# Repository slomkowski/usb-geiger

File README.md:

# USB Geiger counter

2013 Michał Słomkowski

License: GNU GPL v3.0.

This is a repository of a low-cost USB Geiger counter device using STS-5 tube, ATTiny24 and Python-written host software.

Results can be sent to MySQL database, CSV file, ~~xively.com~~ or defined e-mail address if the radiation level is above the defined threshold.

Project was published in Polish hobby electronics periodic: *Elektronika dla Wszystkich* 10/2013, the article [available here](https://serwis.avt.pl/manuals/AVT3074.pdf).

The repository contains:
* *datasheets* - datasheets of components used in the device, especially the Geiger tube
* *firmare* - source code of firmware for ATTiny24, written in C
* *host/geiger-controller* - simple program in C++ for reading data and writing the settings to the device
* *host/geiger-manager* - more complex software written in Python. Periodically reads the data from sensor and sends them to MySQL or CSV file
* *pcb* - printed circuit board layout in Eagle format, schematic in PNG and mirrored board layout for toner transfer

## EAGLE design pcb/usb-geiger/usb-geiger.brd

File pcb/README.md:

USB Geiger counter
==================

2013 Michał Słomkowski

License: GNU GPL v3.0.

This directory holds circuit board files created in Eagle 6 as well as result files: PDF with mirror image and PNG schematic.

Warning! You need commercial version of Eagle to modify the board. Using freeware version, you may be only able to move elements within area of 80 x 100 mm. This restriction doesn't apply to other tasks like printing, exporting or value changing, though.

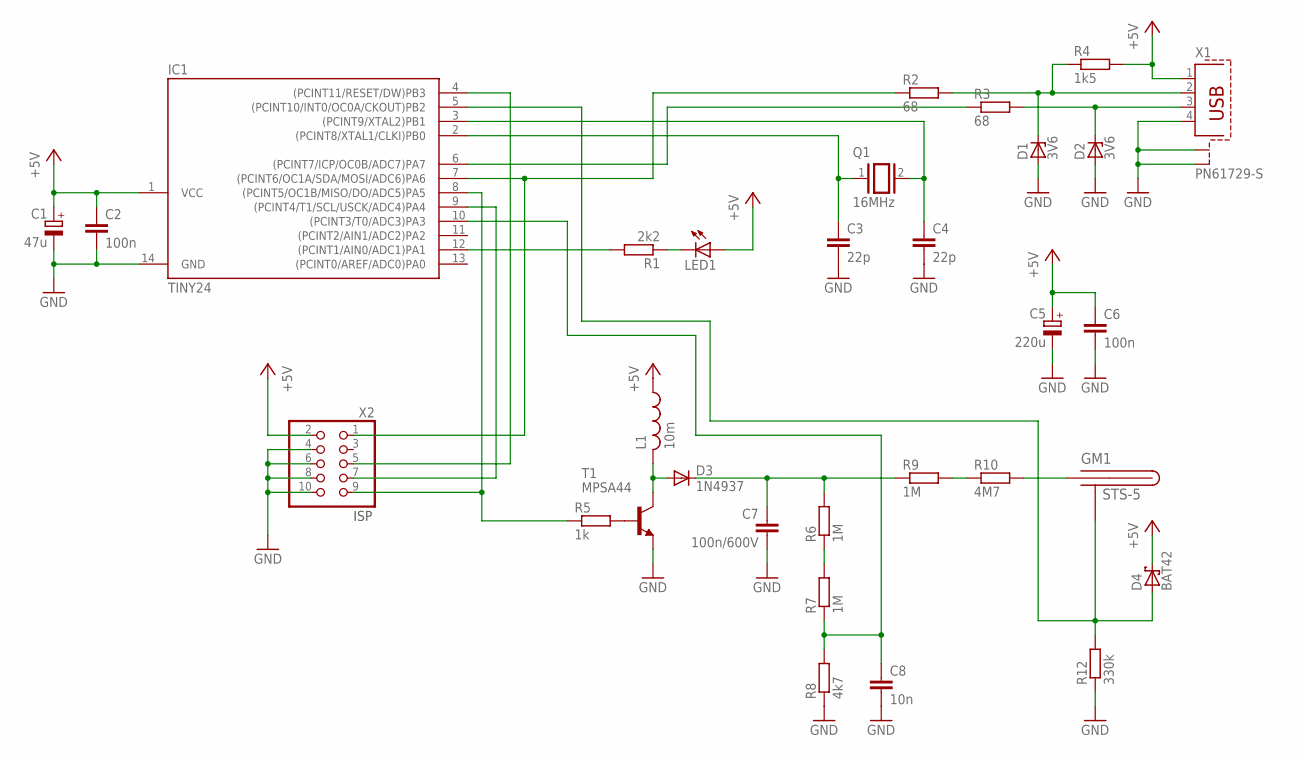
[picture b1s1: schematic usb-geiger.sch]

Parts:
C1: 47u; E2,5-6
C2, C6: 100n; C050-025X075
C3, C4: 22p; C025-025X050
C5: 220u; E5-10,5
C7: 100n/600V; C225-113X268
C8: 10n; C050-025X075
D1, D2: 3V6; DO34Z7
D3: 1N4937; DO41-10
D4: BAT42; DO35-10
GM1: STS-5
IC1: TINY24; DIL14
L1: 10m; 0207/5V
LED1: LED3MM
Q1: 16MHz; QS
R1: 2k2; 0207/10
R2, R3: 68; 0207/10
R4: 1k5; 0207/10
R5: 1k; 0207/10
R6, R7, R9: 1M; 0207/10
R8: 4k7; 0207/10
R10: 4M7; 0207/10
R12: 330k; 0207/10
T1: MPSA44; TO92-EBC
X1: PN61729-S
X2: PINHD-2X5; 2X05

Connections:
+5V: C1.+, C2.1, C5.+, C6.1, D4.C, IC1.1 (VCC), L1.1, LED1.A, R4.2, X1.1, X2.2
GND: C1.-, C2.2, C3.2, C4.2, C5.-, C6.2, C7.2, C8.2, D1.A, D2.A, IC1.14 (GND), R8.1, R12.1, T1.E, X1.4, X1.S1, X1.S2, X2.4, X2.6, X2.8, X2.10
unnamed: R6.1, R7.2
unnamed: D3.A, L1.2, T1.C
unnamed: R5.2, T1.B
unnamed: C7.1, D3.C, R6.2, R9.1
unnamed: R9.2, R10.1
unnamed: GM1.PLUS1 (PLUS), GM1.PLUS2 (PLUS), R10.2
unnamed: C8.1, IC1.10 ((PCINT3/T0/ADC3)PA3), R7.1, R8.2
unnamed: IC1.6 ((PCINT7/ICP/OC0B/ADC7)PA7), R3.1
unnamed: D4.A, GM1.MINUS1 (MINUS), GM1.MINUS2 (MINUS), IC1.5 ((PCINT10/INT0/OC0A/CKOUT)PB2), R12.2
unnamed: IC1.8 ((PCINT5/OC1B/MISO/DO/ADC5)PA5), R5.1, X2.9
unnamed: IC1.7 ((PCINT6/OC1A/SDA/MOSI/ADC6)PA6), R2.1, X2.1
unnamed: IC1.4 ((PCINT11/RESET/DW)PB3), X2.5
unnamed: IC1.9 ((PCINT4/T1/SCL/USCK/ADC4)PA4), X2.7
unnamed: D1.C, R2.2, R4.1, X1.2
unnamed: D2.C, R3.2, X1.3
unnamed: C4.1, IC1.3 ((PCINT9/XTAL2)PB1), Q1.2
unnamed: C3.1, IC1.2 ((PCINT8/XTAL1/CLKI)PB0), Q1.1
unnamed: IC1.12 ((PCINT1/AIN0/ADC1)PA1), R1.2
unnamed: LED1.K (C), R1.1

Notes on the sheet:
ISP

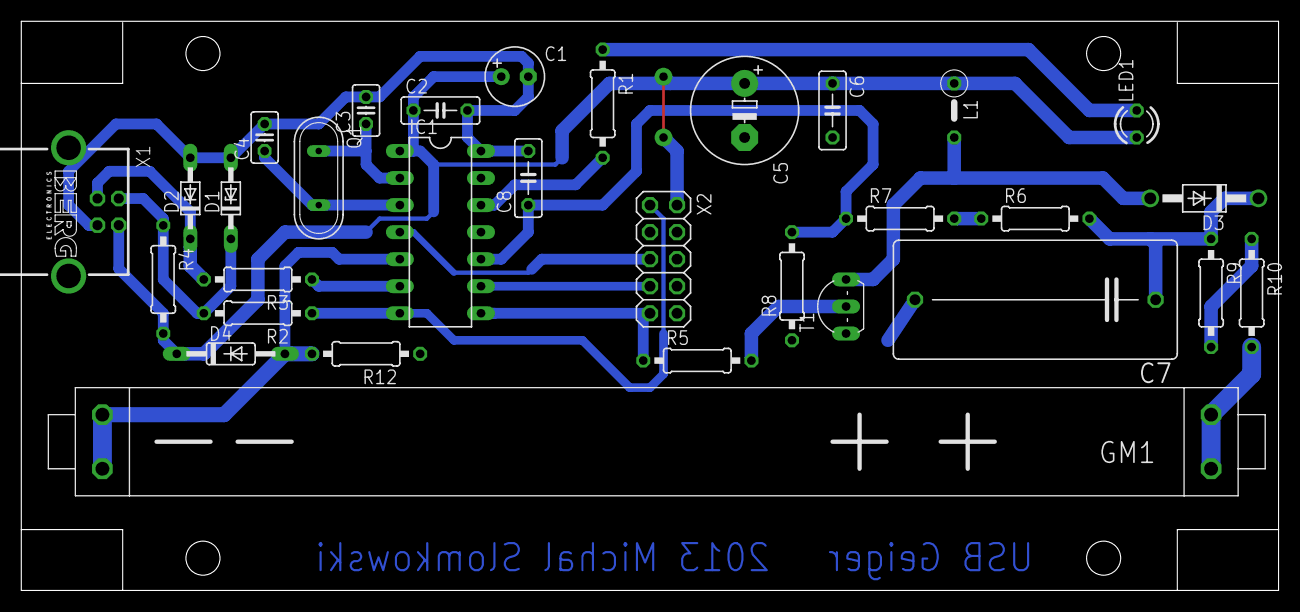
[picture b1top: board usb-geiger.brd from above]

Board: 2 copper layers, 118.1 x 53.5 mm, 31 parts (0 on the bottom side), 21 nets.

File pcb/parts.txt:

Partlist

Exported from usb-geiger.sch at 24-03-2013 21:28

EAGLE Version 6.4.0 Copyright (c) 1988-2013 CadSoft

Assembly variant: 

Part     Value          Device            Package      Library  Sheet

C1       47u            CPOL-EUE2.5-6     E2,5-6       rcl      1
C2       100n           C-EU050-025X075   C050-025X075 rcl      1
C3       22p            C-EU025-025X050   C025-025X050 rcl      1
C4       22p            C-EU025-025X050   C025-025X050 rcl      1
C5       220u           CPOL-EUE5-10.5    E5-10,5      rcl      1
C6       100n           C-EU050-025X075   C050-025X075 rcl      1
C7       100n/600V      C-EU225-113X268   C225-113X268 rcl      1
C8       10n            C-EU050-025X075   C050-025X075 rcl      1
D1       3V6            ZENER-DIODEDO34-7 DO34Z7       diode    1
D2       3V6            ZENER-DIODEDO34-7 DO34Z7       diode    1
D3       1N4937         1N4933            DO41-10      diode    1
D4       BAT42          BAT42             DO35-10      diode    1
GM1      STS-5          STS-5             STS-5        geiger   1
IC1      TINY24         TINY24/44/84-PU   DIL14        avr-7    1
L1       10m            L-US0207/5V       0207/5V      rcl      1
LED1                    LED3MM            LED3MM       led      1
Q1       16MHz          XTAL/S            QS           special  1
R1       2k2            R-EU_0207/10      0207/10      rcl      1
R2       68             R-EU_0207/10      0207/10      rcl      1
R3       68             R-EU_0207/10      0207/10      rcl      1
R4       1k5            R-EU_0207/10      0207/10      rcl      1
R5       1k             R-EU_0207/10      0207/10      rcl      1
R6       1M             R-EU_0207/10      0207/10      rcl      1
R7       1M             R-EU_0207/10      0207/10      rcl      1
R8       4k7            R-EU_0207/10      0207/10      rcl      1
R9       1M             R-EU_0207/10      0207/10      rcl      1
R10      4M7            R-EU_0207/10      0207/10      rcl      1
R12      330k           R-EU_0207/10      0207/10      rcl      1
T1       MPSA44         MPSA44            TO92-EBC     geiger   1
X1       PN61729-S      PN61729-S         PN61729-S    con-berg 1
X2                      PINHD-2X5         2X05         pinhead  1

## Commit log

2013-03-24 First commit. Firmware and board completed and tested. C++ host side completed.
2013-03-24 removed polish sentence
2013-03-24 Geiger-controller: Fix small error with device recognition.
2013-03-25 Added resetting counts value after interval change.
2013-03-25 Descriptions changed.
2013-03-25 Python script for complex management started. Low-level USB interface ready for now.
2013-03-25 README and .gitignore added.
2013-03-25 cosm.com interface ready.
2013-03-26 MySQL updater works. Updaters package extracted.
2013-03-27 main.py ready. GUI and daemon mode to implement.
2013-03-28 Click sound added.
2013-03-28 Monitor works. Need to react on Ctrl-C.
2013-03-29 CSV updater added and ready.
2013-03-29 Exceptions corrected.
2013-03-29 Added daemon mode.
2013-03-29 Timestamp support added to cosm.com and mysql.
2013-03-29 date localtime() fix.
2013-03-29 Fixed local and UTC time issue.
2013-03-29 Round CPM to 1/100
2013-03-30 Fixed error with non-zeroing timer counter variable. Fixed error with ADC init (code redundant). Code optimizing.
2013-03-30 Counter fix.
2013-03-31 Added exception handling for USB errors and reconnection in this case.
2013-04-03 Fixed error with wrong starting interval.
2013-04-04 Added logging, beta.
2013-04-04 Added try-catch in updating procedure.
2013-04-04 Added timeout in cosm.py
2013-04-05 CPM and radiation taken in one usbrequest (get_cpi) instead in two separate.
2013-04-05 Auto loading updater modules in 'updaters' directory.
2013-04-05 Fix.
2013-04-06 Board new pdf.
2013-04-08 Added README in pcb directory.
2013-04-08 Removed GUI from master branch.
2013-04-08 Gitignore.
2013-04-08 Fix for double updater adding.
2013-04-08 Script for starting/stopping app in Debian.
2013-04-09 Fix exception error in cosm.py
2013-04-11 Added readme and changed version to 1.0
2013-04-11 README and configuration_example.ini updated.
2013-07-14 Replaced old name cosm.com to new xively.com
2013-07-14 Updated readme.
2013-07-31 Fixed issue with MySQL - new connection every update.
2013-08-04 Disabled interrupt endpoint in config - saved many bytes of the result file.
2013-08-11 Reenabled interrupt endpoint for compatibility with USB spec.
2013-08-28 Enabled USB_CFG_SUPRESS_INTR_CODE to disable handling interrupt-in transfers. It saves a couple of bytes of program memory.
2013-08-28 .gitignore for Eagle.
2013-08-28 .gitignore
2013-08-28 Added SMTP updater to Geiger manager.
2013-08-28 README files updated to mention e-mail notification.
2014-08-05 Update Debian init script.
2016-03-15 Add package information.
2019-07-29 Update README.
2020-06-29 General cleanup. Implement radmon.org with unit tests. #2
2020-08-02 Implement working GUI app.
2020-08-04 Successfully run fbs (still no USB).
2020-08-04 Sucessfully run from fbs freeze under Windows.
2020-11-25 Add license.
